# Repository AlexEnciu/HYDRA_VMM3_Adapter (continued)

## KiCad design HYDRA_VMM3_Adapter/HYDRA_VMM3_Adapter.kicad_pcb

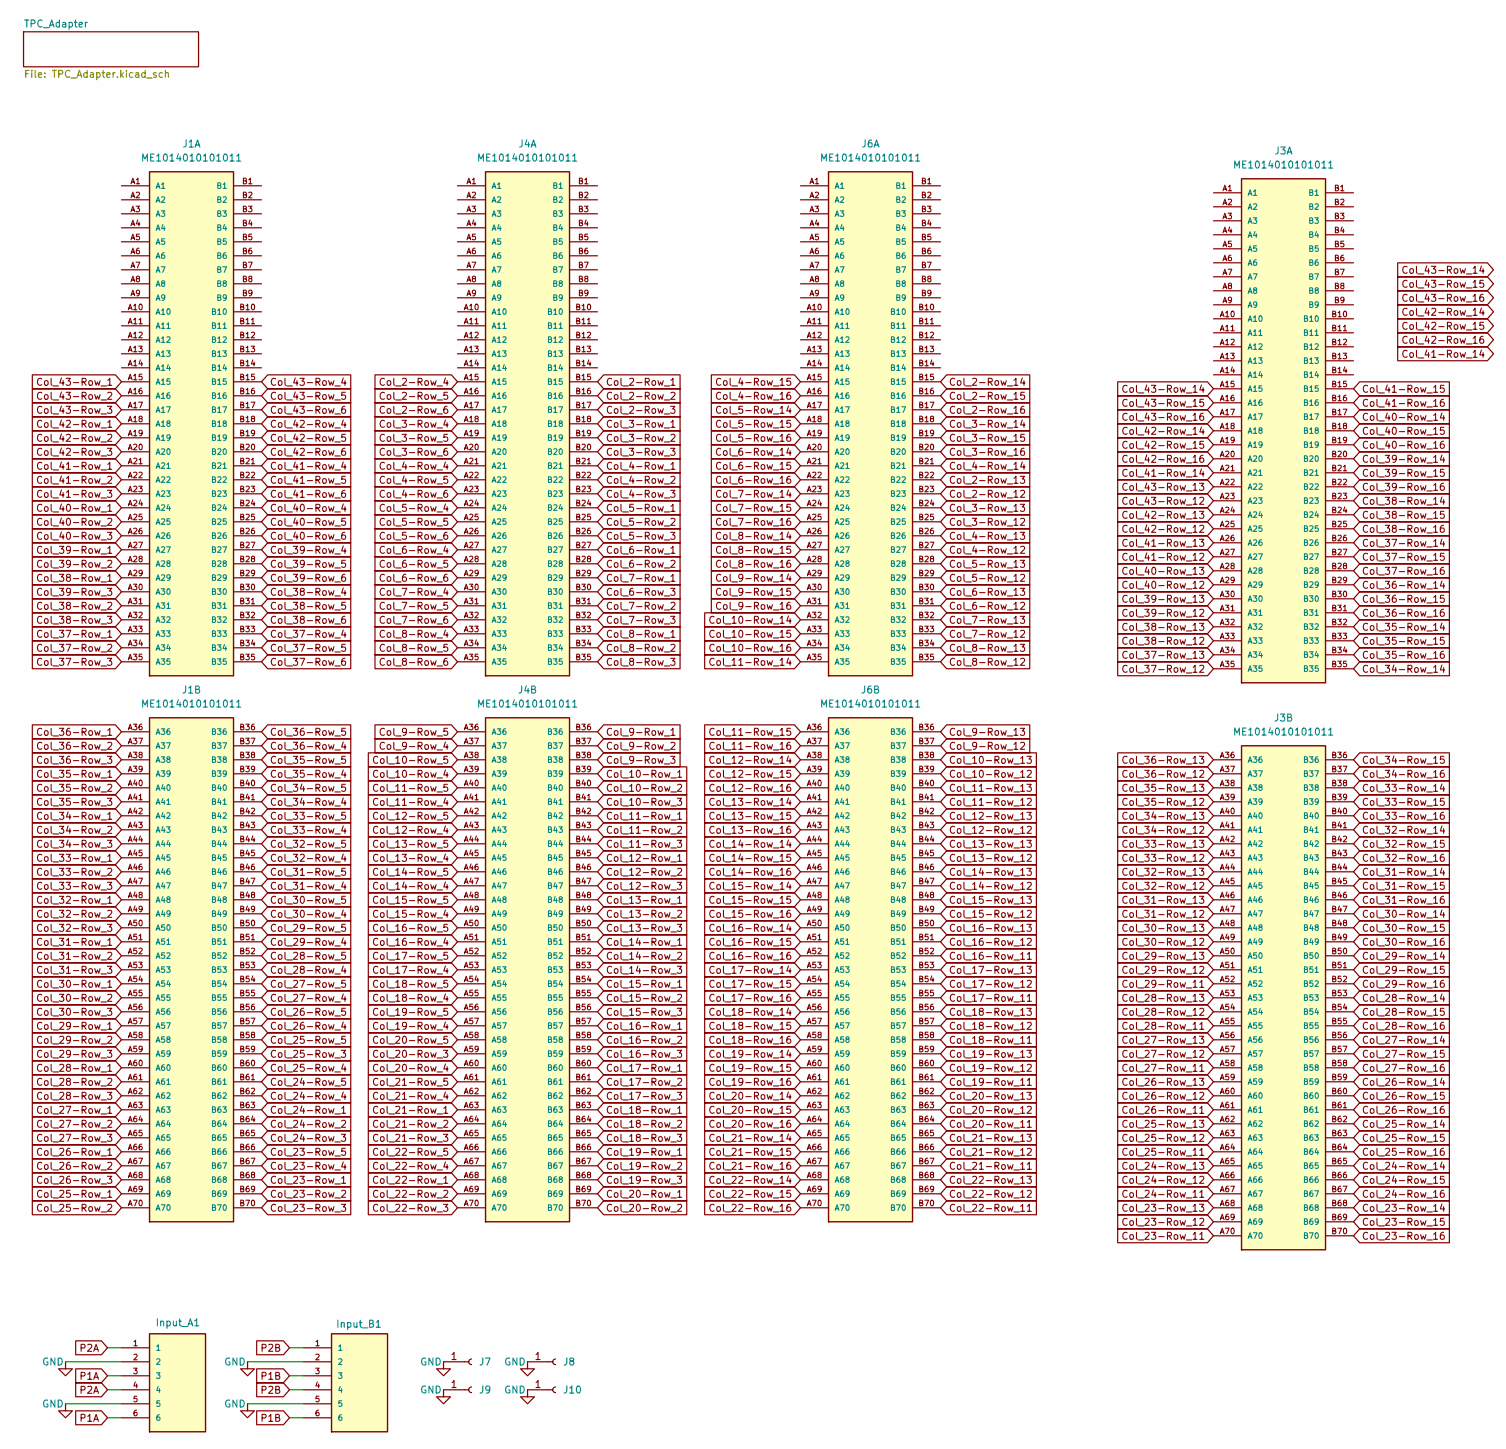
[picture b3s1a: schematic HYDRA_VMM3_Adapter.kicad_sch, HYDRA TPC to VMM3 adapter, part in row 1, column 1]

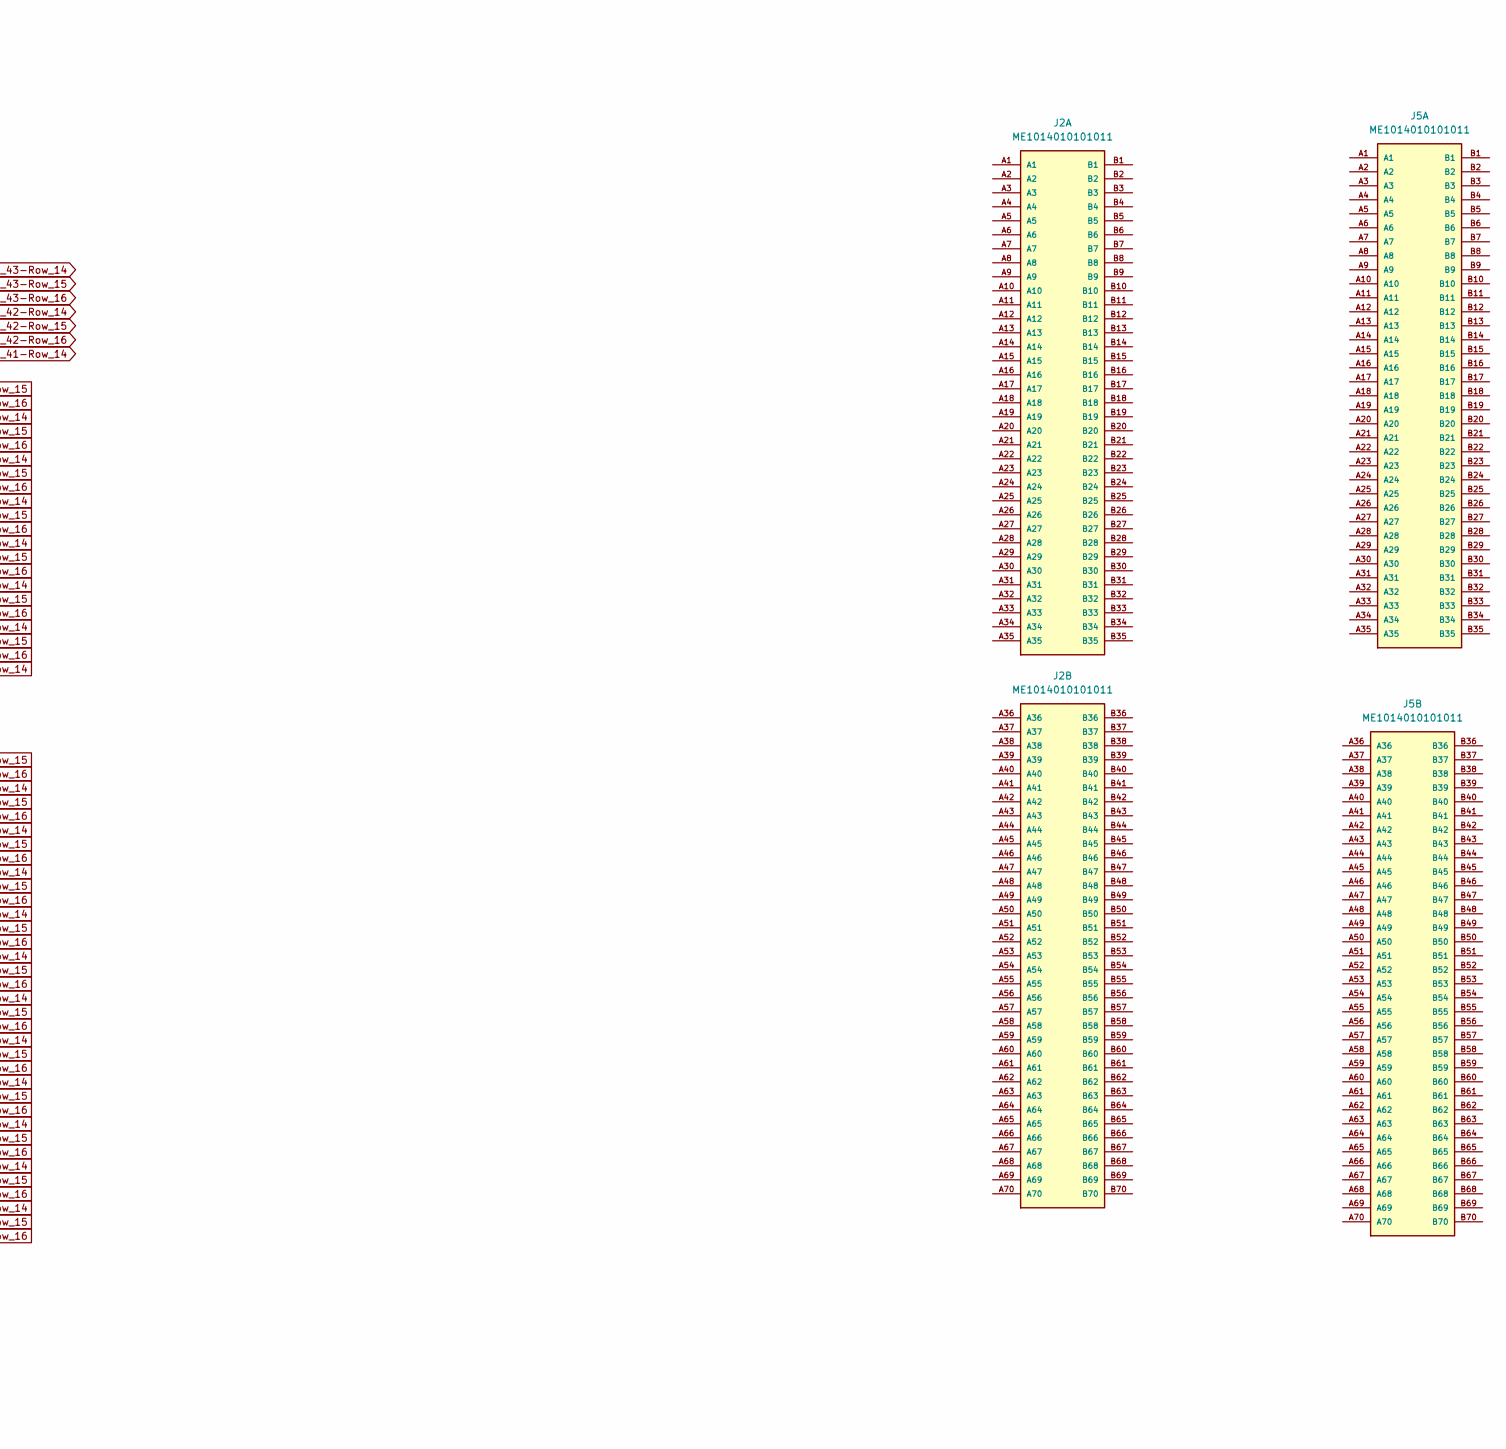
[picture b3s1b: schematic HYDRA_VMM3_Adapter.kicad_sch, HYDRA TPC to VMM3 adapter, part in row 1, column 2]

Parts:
Input_A1: 39-30-1060; MOLEX_39-30-1060; PARTREV A
Input_B1: 39-30-1060; MOLEX_39-30-1060; PARTREV A
J1, J2, J3, J4, J5, J6: ME1014010101011; AMPHENOL_ME1014010101011; PARTREV 11
J7, J8, J9, J10: Conn_01x01_Socket; MountingHole_3.2mm_M3_DIN965_Pad

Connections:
Col_2-Row_1: J4.B15; also elsewhere on the board
Col_2-Row_2: J4.B16; also elsewhere on the board
Col_2-Row_3: J4.B17; also elsewhere on the board
Col_2-Row_4: J4.A15; also elsewhere on the board
Col_2-Row_5: J4.A16; also elsewhere on the board
Col_2-Row_6: J4.A17; also elsewhere on the board
Col_2-Row_12: J6.B23; also elsewhere on the board
Col_2-Row_13: J6.B22; also elsewhere on the board
Col_2-Row_14: J6.B15; also elsewhere on the board
Col_2-Row_15: J6.B16; also elsewhere on the board
Col_2-Row_16: J6.B17; also elsewhere on the board
Col_3-Row_1: J4.B18; also elsewhere on the board
Col_3-Row_2: J4.B19; also elsewhere on the board
Col_3-Row_3: J4.B20; also elsewhere on the board
Col_3-Row_4: J4.A18; also elsewhere on the board
Col_3-Row_5: J4.A19; also elsewhere on the board
Col_3-Row_6: J4.A20; also elsewhere on the board
Col_3-Row_12: J6.B25; also elsewhere on the board
Col_3-Row_13: J6.B24; also elsewhere on the board
Col_3-Row_14: J6.B18; also elsewhere on the board
Col_3-Row_15: J6.B19; also elsewhere on the board
Col_3-Row_16: J6.B20; also elsewhere on the board
Col_4-Row_1: J4.B21; also elsewhere on the board
Col_4-Row_2: J4.B22; also elsewhere on the board
Col_4-Row_3: J4.B23; also elsewhere on the board
Col_4-Row_4: J4.A21; also elsewhere on the board
Col_4-Row_5: J4.A22; also elsewhere on the board
Col_4-Row_6: J4.A23; also elsewhere on the board
Col_4-Row_12: J6.B27; also elsewhere on the board
Col_4-Row_13: J6.B26; also elsewhere on the board
Col_4-Row_14: J6.B21; also elsewhere on the board
Col_4-Row_15: J6.A15; also elsewhere on the board
Col_4-Row_16: J6.A16; also elsewhere on the board
Col_5-Row_1: J4.B24; also elsewhere on the board
Col_5-Row_2: J4.B25; also elsewhere on the board
Col_5-Row_3: J4.B26; also elsewhere on the board
Col_5-Row_4: J4.A24; also elsewhere on the board
Col_5-Row_5: J4.A25; also elsewhere on the board
Col_5-Row_6: J4.A26; also elsewhere on the board
Col_5-Row_12: J6.B29; also elsewhere on the board
Col_5-Row_13: J6.B28; also elsewhere on the board
Col_5-Row_14: J6.A17; also elsewhere on the board
Col_5-Row_15: J6.A18; also elsewhere on the board
Col_5-Row_16: J6.A19; also elsewhere on the board
Col_6-Row_1: J4.B27; also elsewhere on the board
Col_6-Row_2: J4.B28; also elsewhere on the board
Col_6-Row_3: J4.B30; also elsewhere on the board
Col_6-Row_4: J4.A27; also elsewhere on the board
Col_6-Row_5: J4.A28; also elsewhere on the board
Col_6-Row_6: J4.A29; also elsewhere on the board
Col_6-Row_12: J6.B31; also elsewhere on the board
Col_6-Row_13: J6.B30; also elsewhere on the board
Col_6-Row_14: J6.A20; also elsewhere on the board
Col_6-Row_15: J6.A21; also elsewhere on the board
Col_6-Row_16: J6.A22; also elsewhere on the board
Col_7-Row_1: J4.B29; also elsewhere on the board
Col_7-Row_2: J4.B31; also elsewhere on the board
Col_7-Row_3: J4.B32; also elsewhere on the board
Col_7-Row_4: J4.A30; also elsewhere on the board
Col_7-Row_5: J4.A31; also elsewhere on the board
Col_7-Row_6: J4.A32; also elsewhere on the board
Col_7-Row_12: J6.B33; also elsewhere on the board
Col_7-Row_13: J6.B32; also elsewhere on the board
Col_7-Row_14: J6.A23; also elsewhere on the board
Col_7-Row_15: J6.A24; also elsewhere on the board
Col_7-Row_16: J6.A25; also elsewhere on the board
Col_8-Row_1: J4.B33; also elsewhere on the board
Col_8-Row_2: J4.B34; also elsewhere on the board
Col_8-Row_3: J4.B35; also elsewhere on the board
Col_8-Row_4: J4.A33; also elsewhere on the board
Col_8-Row_5: J4.A34; also elsewhere on the board
Col_8-Row_6: J4.A35; also elsewhere on the board
Col_8-Row_12: J6.B35; also elsewhere on the board
Col_8-Row_13: J6.B34; also elsewhere on the board
Col_8-Row_14: J6.A26; also elsewhere on the board
Col_8-Row_15: J6.A27; also elsewhere on the board
Col_8-Row_16: J6.A28; also elsewhere on the board
Col_9-Row_1: J4.B36; also elsewhere on the board
Col_9-Row_2: J4.B37; also elsewhere on the board
Col_9-Row_3: J4.B38; also elsewhere on the board
Col_9-Row_4: J4.A37; also elsewhere on the board
Col_9-Row_5: J4.A36; also elsewhere on the board
Col_9-Row_12: J6.B37; also elsewhere on the board
Col_9-Row_13: J6.B36; also elsewhere on the board
Col_9-Row_14: J6.A29; also elsewhere on the board
Col_9-Row_15: J6.A30; also elsewhere on the board
Col_9-Row_16: J6.A31; also elsewhere on the board
Col_10-Row_1: J4.B39; also elsewhere on the board
Col_10-Row_2: J4.B40; also elsewhere on the board
Col_10-Row_3: J4.B41; also elsewhere on the board
Col_10-Row_4: J4.A39; also elsewhere on the board
Col_10-Row_5: J4.A38; also elsewhere on the board
Col_10-Row_12: J6.B39; also elsewhere on the board
Col_10-Row_13: J6.B38; also elsewhere on the board
Col_10-Row_14: J6.A32; also elsewhere on the board
Col_10-Row_15: J6.A33; also elsewhere on the board
Col_10-Row_16: J6.A34; also elsewhere on the board
Col_11-Row_1: J4.B42; also elsewhere on the board
Col_11-Row_2: J4.B43; also elsewhere on the board
Col_11-Row_3: J4.B44; also elsewhere on the board
Col_11-Row_4: J4.A41; also elsewhere on the board
Col_11-Row_5: J4.A40; also elsewhere on the board
Col_11-Row_12: J6.B41; also elsewhere on the board
Col_11-Row_13: J6.B40; also elsewhere on the board
Col_11-Row_14: J6.A35; also elsewhere on the board
Col_11-Row_15: J6.A36; also elsewhere on the board
Col_11-Row_16: J6.A37; also elsewhere on the board
Col_12-Row_1: J4.B45; also elsewhere on the board
Col_12-Row_2: J4.B46; also elsewhere on the board
Col_12-Row_3: J4.B47; also elsewhere on the board
Col_12-Row_4: J4.A43; also elsewhere on the board
Col_12-Row_5: J4.A42; also elsewhere on the board
Col_12-Row_12: J6.B43; also elsewhere on the board
Col_12-Row_13: J6.B42; also elsewhere on the board
Col_12-Row_14: J6.A38; also elsewhere on the board
Col_12-Row_15: J6.A39; also elsewhere on the board
Col_12-Row_16: J6.A40; also elsewhere on the board
Col_13-Row_1: J4.B48; also elsewhere on the board
Col_13-Row_2: J4.B49; also elsewhere on the board
Col_13-Row_3: J4.B50; also elsewhere on the board
Col_13-Row_4: J4.A45; also elsewhere on the board
Col_13-Row_5: J4.A44; also elsewhere on the board
Col_13-Row_12: J6.B45; also elsewhere on the board
Col_13-Row_13: J6.B44; also elsewhere on the board
Col_13-Row_14: J6.A41; also elsewhere on the board
Col_13-Row_15: J6.A42; also elsewhere on the board
Col_13-Row_16: J6.A43; also elsewhere on the board
Col_14-Row_1: J4.B51; also elsewhere on the board
Col_14-Row_2: J4.B52; also elsewhere on the board
Col_14-Row_3: J4.B53; also elsewhere on the board
Col_14-Row_4: J4.A47; also elsewhere on the board
Col_14-Row_5: J4.A46; also elsewhere on the board
Col_14-Row_12: J6.B47; also elsewhere on the board
Col_14-Row_13: J6.B46; also elsewhere on the board
Col_14-Row_14: J6.A44; also elsewhere on the board
Col_14-Row_15: J6.A45; also elsewhere on the board
Col_14-Row_16: J6.A46; also elsewhere on the board
Col_15-Row_1: J4.B54; also elsewhere on the board
Col_15-Row_2: J4.B55; also elsewhere on the board
Col_15-Row_3: J4.B56; also elsewhere on the board
Col_15-Row_4: J4.A49; also elsewhere on the board
Col_15-Row_5: J4.A48; also elsewhere on the board
Col_15-Row_12: J6.B49; also elsewhere on the board
Col_15-Row_13: J6.B48; also elsewhere on the board
Col_15-Row_14: J6.A47; also elsewhere on the board
Col_15-Row_15: J6.A48; also elsewhere on the board
Col_15-Row_16: J6.A49; also elsewhere on the board
Col_16-Row_1: J4.B57; also elsewhere on the board
Col_16-Row_2: J4.B58; also elsewhere on the board
Col_16-Row_3: J4.B59; also elsewhere on the board
Col_16-Row_4: J4.A51; also elsewhere on the board
Col_16-Row_5: J4.A50; also elsewhere on the board
Col_16-Row_11: J6.B52; also elsewhere on the board
Col_16-Row_12: J6.B51; also elsewhere on the board
Col_16-Row_13: J6.B50; also elsewhere on the board
Col_16-Row_14: J6.A50; also elsewhere on the board
Col_16-Row_15: J6.A51; also elsewhere on the board
Col_16-Row_16: J6.A52; also elsewhere on the board
Col_17-Row_1: J4.B60; also elsewhere on the board
Col_17-Row_2: J4.B61; also elsewhere on the board
Col_17-Row_3: J4.B62; also elsewhere on the board
Col_17-Row_4: J4.A53; also elsewhere on the board
Col_17-Row_5: J4.A52; also elsewhere on the board
Col_17-Row_11: J6.B55; also elsewhere on the board
Col_17-Row_12: J6.B54; also elsewhere on the board
Col_17-Row_13: J6.B53; also elsewhere on the board
Col_17-Row_14: J6.A53; also elsewhere on the board
Col_17-Row_15: J6.A54; also elsewhere on the board
Col_17-Row_16: J6.A55; also elsewhere on the board
Col_18-Row_1: J4.B63; also elsewhere on the board
Col_18-Row_2: J4.B64; also elsewhere on the board
Col_18-Row_3: J4.B65; also elsewhere on the board
Col_18-Row_4: J4.A55; also elsewhere on the board
Col_18-Row_5: J4.A54; also elsewhere on the board
Col_18-Row_11: J6.B58; also elsewhere on the board
Col_18-Row_12: J6.B57; also elsewhere on the board
Col_18-Row_13: J6.B56; also elsewhere on the board
Col_18-Row_14: J6.A56; also elsewhere on the board
Col_18-Row_15: J6.A57; also elsewhere on the board
Col_18-Row_16: J6.A58; also elsewhere on the board
Col_19-Row_1: J4.B66; also elsewhere on the board
Col_19-Row_2: J4.B67; also elsewhere on the board
Col_19-Row_3: J4.B68; also elsewhere on the board
Col_19-Row_4: J4.A57; also elsewhere on the board
Col_19-Row_5: J4.A56; also elsewhere on the board
Col_19-Row_11: J6.B61; also elsewhere on the board
Col_19-Row_12: J6.B60; also elsewhere on the board
Col_19-Row_13: J6.B59; also elsewhere on the board
Col_19-Row_14: J6.A59; also elsewhere on the board
Col_19-Row_15: J6.A60; also elsewhere on the board
Col_19-Row_16: J6.A61; also elsewhere on the board
Col_20-Row_1: J4.B69; also elsewhere on the board
Col_20-Row_2: J4.B70; also elsewhere on the board
Col_20-Row_3: J4.A59; also elsewhere on the board
Col_20-Row_4: J4.A60; also elsewhere on the board
Col_20-Row_5: J4.A58; also elsewhere on the board
Col_20-Row_11: J6.B64; also elsewhere on the board
Col_20-Row_12: J6.B63; also elsewhere on the board
Col_20-Row_13: J6.B62; also elsewhere on the board
Col_20-Row_14: J6.A62; also elsewhere on the board
Col_20-Row_15: J6.A63; also elsewhere on the board
Col_20-Row_16: J6.A64; also elsewhere on the board
Col_21-Row_1: J4.A63; also elsewhere on the board
Col_21-Row_2: J4.A64; also elsewhere on the board
Col_21-Row_3: J4.A65; also elsewhere on the board
Col_21-Row_4: J4.A62; also elsewhere on the board
Col_21-Row_5: J4.A61; also elsewhere on the board
Col_21-Row_11: J6.B67; also elsewhere on the board
Col_21-Row_12: J6.B66; also elsewhere on the board
Col_21-Row_13: J6.B65; also elsewhere on the board
Col_21-Row_14: J6.A65; also elsewhere on the board
Col_21-Row_15: J6.A66; also elsewhere on the board
Col_21-Row_16: J6.A67; also elsewhere on the board
Col_22-Row_1: J4.A68; also elsewhere on the board
Col_22-Row_2: J4.A69; also elsewhere on the board
Col_22-Row_3: J4.A70; also elsewhere on the board
Col_22-Row_4: J4.A67; also elsewhere on the board
Col_22-Row_5: J4.A66; also elsewhere on the board
Col_22-Row_11: J6.B70; also elsewhere on the board
Col_22-Row_12: J6.B69; also elsewhere on the board
Col_22-Row_13: J6.B68; also elsewhere on the board
Col_22-Row_14: J6.A68; also elsewhere on the board
Col_22-Row_15: J6.A69; also elsewhere on the board
Col_22-Row_16: J6.A70; also elsewhere on the board
Col_23-Row_1: J1.B68; also elsewhere on the board
Col_23-Row_2: J1.B69; also elsewhere on the board
Col_23-Row_3: J1.B70; also elsewhere on the board
Col_23-Row_4: J1.B67; also elsewhere on the board
Col_23-Row_5: J1.B66; also elsewhere on the board
Col_23-Row_11: J3.A70; also elsewhere on the board
Col_23-Row_12: J3.A69; also elsewhere on the board
Col_23-Row_13: J3.A68; also elsewhere on the board
Col_23-Row_14: J3.B68; also elsewhere on the board
Col_23-Row_15: J3.B69; also elsewhere on the board
Col_23-Row_16: J3.B70; also elsewhere on the board
Col_24-Row_1: J1.B63; also elsewhere on the board
Col_24-Row_2: J1.B64; also elsewhere on the board
Col_24-Row_3: J1.B65; also elsewhere on the board
Col_24-Row_4: J1.B62; also elsewhere on the board
Col_24-Row_5: J1.B61; also elsewhere on the board
Col_24-Row_11: J3.A67; also elsewhere on the board
Col_24-Row_12: J3.A66; also elsewhere on the board
Col_24-Row_13: J3.A65; also elsewhere on the board
Col_24-Row_14: J3.B65; also elsewhere on the board
Col_24-Row_15: J3.B66; also elsewhere on the board
Col_24-Row_16: J3.B67; also elsewhere on the board
Col_25-Row_1: J1.A69; also elsewhere on the board
Col_25-Row_2: J1.A70; also elsewhere on the board
Col_25-Row_3: J1.B59; also elsewhere on the board
Col_25-Row_4: J1.B60; also elsewhere on the board
Col_25-Row_5: J1.B58; also elsewhere on the board
Col_25-Row_11: J3.A64; also elsewhere on the board
Col_25-Row_12: J3.A63; also elsewhere on the board
Col_25-Row_13: J3.A62; also elsewhere on the board
Col_25-Row_14: J3.B62; also elsewhere on the board
Col_25-Row_15: J3.B63; also elsewhere on the board
Col_25-Row_16: J3.B64; also elsewhere on the board
Col_26-Row_1: J1.A66; also elsewhere on the board
Col_26-Row_2: J1.A67; also elsewhere on the board
Col_26-Row_3: J1.A68; also elsewhere on the board
Col_26-Row_4: J1.B57; also elsewhere on the board
Col_26-Row_5: J1.B56; also elsewhere on the board
Col_26-Row_11: J3.A61; also elsewhere on the board
Col_26-Row_12: J3.A60; also elsewhere on the board
Col_26-Row_13: J3.A59; also elsewhere on the board
Col_26-Row_14: J3.B59; also elsewhere on the board
Col_26-Row_15: J3.B60; also elsewhere on the board
Col_26-Row_16: J3.B61; also elsewhere on the board
Col_27-Row_1: J1.A63; also elsewhere on the board
Col_27-Row_2: J1.A64; also elsewhere on the board
Col_27-Row_3: J1.A65; also elsewhere on the board
Col_27-Row_4: J1.B55; also elsewhere on the board
Col_27-Row_5: J1.B54; also elsewhere on the board
Col_27-Row_11: J3.A58; also elsewhere on the board
Col_27-Row_12: J3.A57; also elsewhere on the board
Col_27-Row_13: J3.A56; also elsewhere on the board
Col_27-Row_14: J3.B56; also elsewhere on the board
Col_27-Row_15: J3.B57; also elsewhere on the board
Col_27-Row_16: J3.B58; also elsewhere on the board
Col_28-Row_1: J1.A60; also elsewhere on the board
Col_28-Row_2: J1.A61; also elsewhere on the board
Col_28-Row_3: J1.A62; also elsewhere on the board
Col_28-Row_4: J1.B53; also elsewhere on the board
Col_28-Row_5: J1.B52; also elsewhere on the board
Col_28-Row_11: J3.A55; also elsewhere on the board
Col_28-Row_12: J3.A54; also elsewhere on the board
Col_28-Row_13: J3.A53; also elsewhere on the board
Col_28-Row_14: J3.B53; also elsewhere on the board
Col_28-Row_15: J3.B54; also elsewhere on the board
Col_28-Row_16: J3.B55; also elsewhere on the board
Col_29-Row_1: J1.A57; also elsewhere on the board
Col_29-Row_2: J1.A58; also elsewhere on the board
Col_29-Row_3: J1.A59; also elsewhere on the board
Col_29-Row_4: J1.B51; also elsewhere on the board
Col_29-Row_5: J1.B50; also elsewhere on the board
Col_29-Row_11: J3.A52; also elsewhere on the board
Col_29-Row_12: J3.A51; also elsewhere on the board
Col_29-Row_13: J3.A50; also elsewhere on the board
Col_29-Row_14: J3.B50; also elsewhere on the board
Col_29-Row_15: J3.B51; also elsewhere on the board
Col_29-Row_16: J3.B52; also elsewhere on the board
Col_30-Row_1: J1.A54; also elsewhere on the board
Col_30-Row_2: J1.A55; also elsewhere on the board
Col_30-Row_3: J1.A56; also elsewhere on the board
Col_30-Row_4: J1.B49; also elsewhere on the board
Col_30-Row_5: J1.B48; also elsewhere on the board
Col_30-Row_12: J3.A49; also elsewhere on the board
Col_30-Row_13: J3.A48; also elsewhere on the board
Col_30-Row_14: J3.B47; also elsewhere on the board
Col_30-Row_15: J3.B48; also elsewhere on the board
Col_30-Row_16: J3.B49; also elsewhere on the board
Col_31-Row_1: J1.A51; also elsewhere on the board
Col_31-Row_2: J1.A52; also elsewhere on the board
Col_31-Row_3: J1.A53; also elsewhere on the board
Col_31-Row_4: J1.B47; also elsewhere on the board
Col_31-Row_5: J1.B46; also elsewhere on the board
Col_31-Row_12: J3.A47; also elsewhere on the board
Col_31-Row_13: J3.A46; also elsewhere on the board
Col_31-Row_14: J3.B44; also elsewhere on the board
Col_31-Row_15: J3.B45; also elsewhere on the board
Col_31-Row_16: J3.B46; also elsewhere on the board
Col_32-Row_1: J1.A48; also elsewhere on the board
Col_32-Row_2: J1.A49; also elsewhere on the board
Col_32-Row_3: J1.A50; also elsewhere on the board
Col_32-Row_4: J1.B45; also elsewhere on the board
Col_32-Row_5: J1.B44; also elsewhere on the board
Col_32-Row_12: J3.A45; also elsewhere on the board
Col_32-Row_13: J3.A44; also elsewhere on the board
Col_32-Row_14: J3.B41; also elsewhere on the board
Col_32-Row_15: J3.B42; also elsewhere on the board
Col_32-Row_16: J3.B43; also elsewhere on the board
Col_33-Row_1: J1.A45; also elsewhere on the board
Col_33-Row_2: J1.A46; also elsewhere on the board
Col_33-Row_3: J1.A47; also elsewhere on the board
Col_33-Row_4: J1.B43; also elsewhere on the board
Col_33-Row_5: J1.B42; also elsewhere on the board
Col_33-Row_12: J3.A43; also elsewhere on the board
Col_33-Row_13: J3.A42; also elsewhere on the board
Col_33-Row_14: J3.B38; also elsewhere on the board
Col_33-Row_15: J3.B39; also elsewhere on the board
Col_33-Row_16: J3.B40; also elsewhere on the board
Col_34-Row_1: J1.A42; also elsewhere on the board
Col_34-Row_2: J1.A43; also elsewhere on the board
Col_34-Row_3: J1.A44; also elsewhere on the board
Col_34-Row_4: J1.B41; also elsewhere on the board
Col_34-Row_5: J1.B40; also elsewhere on the board
Col_34-Row_12: J3.A41; also elsewhere on the board
Col_34-Row_13: J3.A40; also elsewhere on the board
Col_34-Row_14: J3.B35; also elsewhere on the board
Col_34-Row_15: J3.B36; also elsewhere on the board
Col_34-Row_16: J3.B37; also elsewhere on the board
Col_35-Row_1: J1.A39; also elsewhere on the board
Col_35-Row_2: J1.A40; also elsewhere on the board
Col_35-Row_3: J1.A41; also elsewhere on the board
Col_35-Row_4: J1.B39; also elsewhere on the board
Col_35-Row_5: J1.B38; also elsewhere on the board
Col_35-Row_12: J3.A39; also elsewhere on the board
Col_35-Row_13: J3.A38; also elsewhere on the board
Col_35-Row_14: J3.B32; also elsewhere on the board
Col_35-Row_15: J3.B33; also elsewhere on the board
Col_35-Row_16: J3.B34; also elsewhere on the board
Col_36-Row_1: J1.A36; also elsewhere on the board
Col_36-Row_2: J1.A37; also elsewhere on the board
Col_36-Row_3: J1.A38; also elsewhere on the board
Col_36-Row_4: J1.B37; also elsewhere on the board
Col_36-Row_5: J1.B36; also elsewhere on the board
Col_36-Row_12: J3.A37; also elsewhere on the board
Col_36-Row_13: J3.A36; also elsewhere on the board
Col_36-Row_14: J3.B29; also elsewhere on the board
Col_36-Row_15: J3.B30; also elsewhere on the board
Col_36-Row_16: J3.B31; also elsewhere on the board
Col_37-Row_1: J1.A33; also elsewhere on the board
Col_37-Row_2: J1.A34; also elsewhere on the board
Col_37-Row_3: J1.A35; also elsewhere on the board
Col_37-Row_4: J1.B33; also elsewhere on the board
Col_37-Row_5: J1.B34; also elsewhere on the board
Col_37-Row_6: J1.B35; also elsewhere on the board
Col_37-Row_12: J3.A35; also elsewhere on the board
Col_37-Row_13: J3.A34; also elsewhere on the board
Col_37-Row_14: J3.B26; also elsewhere on the board
Col_37-Row_15: J3.B27; also elsewhere on the board
Col_37-Row_16: J3.B28; also elsewhere on the board
Col_38-Row_1: J1.A29; also elsewhere on the board
Col_38-Row_2: J1.A31; also elsewhere on the board
Col_38-Row_3: J1.A32; also elsewhere on the board
Col_38-Row_4: J1.B30; also elsewhere on the board
Col_38-Row_5: J1.B31; also elsewhere on the board
Col_38-Row_6: J1.B32; also elsewhere on the board
Col_38-Row_12: J3.A33; also elsewhere on the board
Col_38-Row_13: J3.A32; also elsewhere on the board
Col_38-Row_14: J3.B23; also elsewhere on the board
Col_38-Row_15: J3.B24; also elsewhere on the board
Col_38-Row_16: J3.B25; also elsewhere on the board
Col_39-Row_1: J1.A27; also elsewhere on the board
Col_39-Row_2: J1.A28; also elsewhere on the board
Col_39-Row_3: J1.A30; also elsewhere on the board
Col_39-Row_4: J1.B27; also elsewhere on the board
Col_39-Row_5: J1.B28; also elsewhere on the board
Col_39-Row_6: J1.B29; also elsewhere on the board
Col_39-Row_12: J3.A31; also elsewhere on the board
Col_39-Row_13: J3.A30; also elsewhere on the board
Col_39-Row_14: J3.B20; also elsewhere on the board
Col_39-Row_15: J3.B21; also elsewhere on the board
Col_39-Row_16: J3.B22; also elsewhere on the board
Col_40-Row_1: J1.A24; also elsewhere on the board
Col_40-Row_2: J1.A25; also elsewhere on the board
Col_40-Row_3: J1.A26; also elsewhere on the board
Col_40-Row_4: J1.B24; also elsewhere on the board
Col_40-Row_5: J1.B25; also elsewhere on the board
Col_40-Row_6: J1.B26; also elsewhere on the board
Col_40-Row_12: J3.A29; also elsewhere on the board
Col_40-Row_13: J3.A28; also elsewhere on the board
Col_40-Row_14: J3.B17; also elsewhere on the board
Col_40-Row_15: J3.B18; also elsewhere on the board
Col_40-Row_16: J3.B19; also elsewhere on the board
Col_41-Row_1: J1.A21; also elsewhere on the board
Col_41-Row_2: J1.A22; also elsewhere on the board
Col_41-Row_3: J1.A23; also elsewhere on the board
Col_41-Row_4: J1.B21; also elsewhere on the board
Col_41-Row_5: J1.B22; also elsewhere on the board
Col_41-Row_6: J1.B23; also elsewhere on the board
Col_41-Row_12: J3.A27; also elsewhere on the board
Col_41-Row_13: J3.A26; also elsewhere on the board
Col_41-Row_14: J3.A21; also elsewhere on the board
Col_41-Row_15: J3.B15; also elsewhere on the board
Col_41-Row_16: J3.B16; also elsewhere on the board
Col_42-Row_1: J1.A18; also elsewhere on the board
Col_42-Row_2: J1.A19; also elsewhere on the board
Col_42-Row_3: J1.A20; also elsewhere on the board
Col_42-Row_4: J1.B18; also elsewhere on the board
Col_42-Row_5: J1.B19; also elsewhere on the board
Col_42-Row_6: J1.B20; also elsewhere on the board
Col_42-Row_12: J3.A25; also elsewhere on the board
Col_42-Row_13: J3.A24; also elsewhere on the board
Col_42-Row_14: J3.A18; also elsewhere on the board
Col_42-Row_15: J3.A19; also elsewhere on the board
Col_42-Row_16: J3.A20; also elsewhere on the board
Col_43-Row_1: J1.A15; also elsewhere on the board
Col_43-Row_2: J1.A16; also elsewhere on the board
Col_43-Row_3: J1.A17; also elsewhere on the board
Col_43-Row_4: J1.B15; also elsewhere on the board
Col_43-Row_5: J1.B16; also elsewhere on the board
Col_43-Row_6: J1.B17; also elsewhere on the board
Col_43-Row_12: J3.A23; also elsewhere on the board
Col_43-Row_13: J3.A22; also elsewhere on the board
Col_43-Row_14: J3.A15; also elsewhere on the board
Col_43-Row_15: J3.A16; also elsewhere on the board
Col_43-Row_16: J3.A17; also elsewhere on the board
GND: Input_A1.2, Input_A1.5, Input_B1.2, Input_B1.5, J7.1, J8.1, J9.1, J10.1; also elsewhere on the board
P1A: Input_A1.3, Input_A1.6
P1B: Input_B1.3, Input_B1.6
P2A: Input_A1.1, Input_A1.4
P2B: Input_B1.1, Input_B1.4
